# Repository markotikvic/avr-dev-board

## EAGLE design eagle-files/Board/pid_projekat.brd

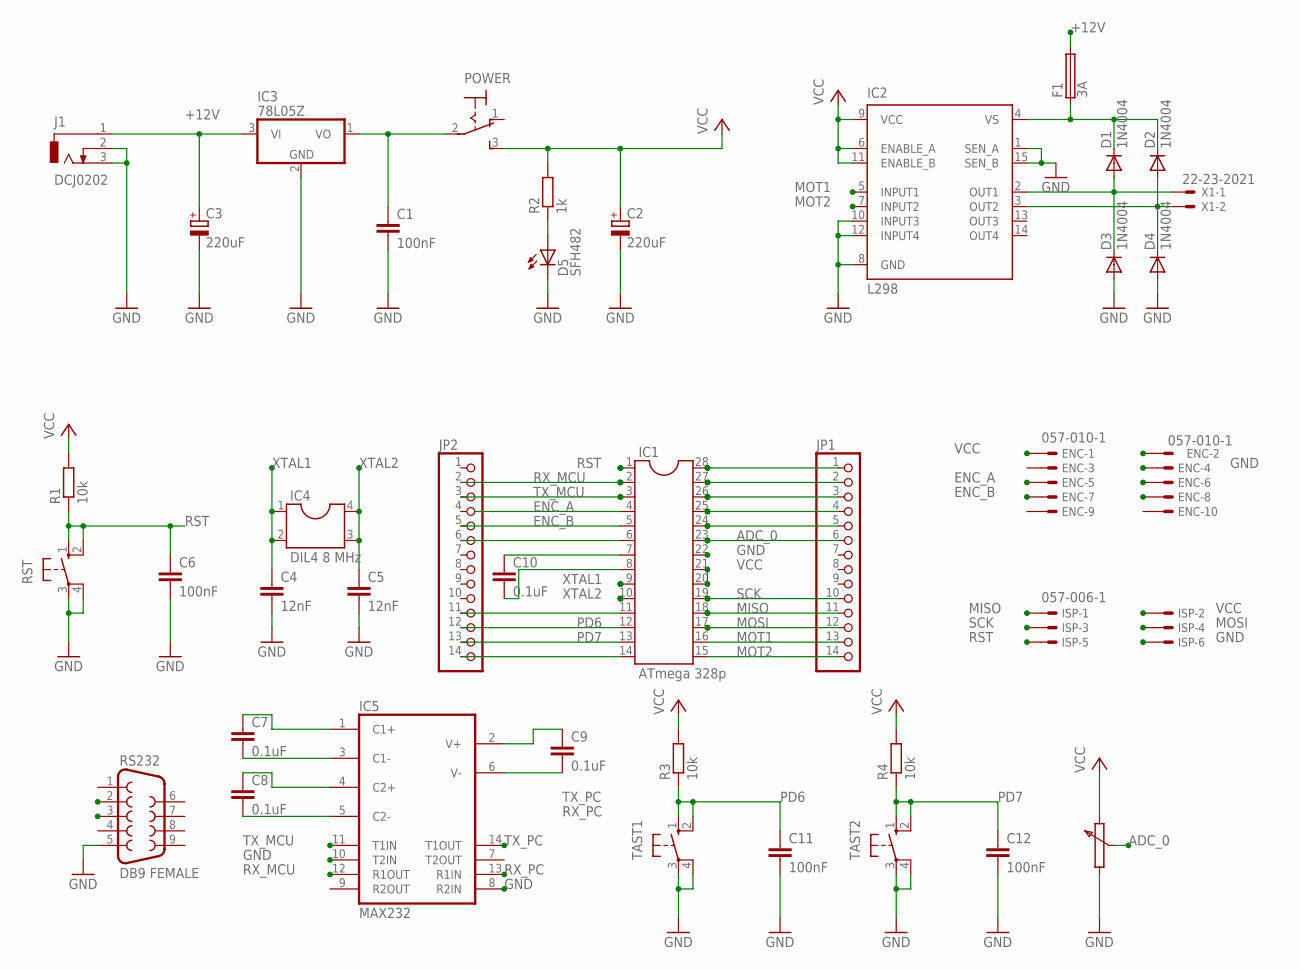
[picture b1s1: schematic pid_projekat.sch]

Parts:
C1, C6, C11, C12: 100nF; C2.5-3
C2, C3: 220uF; E2,5-6E
C4, C5: 12nF; C2.5-3
C7, C8, C9, C10: 0.1uF; C2.5-3
D1, D2, D3, D4: 1N4004; DO41-10
D5: SFH482
ENC: 057-010-1
F1: 3A; GSH15
IC1: ATmega 328p; DIL28-6
IC2: L298; MULTIWATT-15
IC3: 78L05Z; TO92
IC4: DIL4 8 MHz; DIL04
IC5: MAX232; DIL16
ISP: 057-006-1
J1: DCJ0202
JP1, JP2: PINHD-1X14; 1X14
POWER: 320-916
R1, R3, R4: 10k; 0204/7
R2: 1k; 0204/7
RS232: DB9 FEMALE; F09HP
RST: 10-XX; B3F-10XX
TAST1, TAST2: 10-XX; B3F-10XX
X1: 22-23-2021

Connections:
+12V: C3.+, F1.2, IC3.3 (VI), J1.1
ADC_0: IC1.23, JP1.6
ENC_A: ENC.5, IC1.4, IC1.26, JP1.3
ENC_AINV: ENC.6, IC1.24, JP1.5
ENC_B: ENC.7, IC1.5, IC1.25, JP1.4, JP2.5
ENC_BINV: ENC.8
GND: C1.2, C2.-, C3.-, C4.2, C5.2, C6.2, C11.2, C12.2, D3.A, D4.A, D5.K (C), ENC.4, IC1.22, IC2.1 (SEN_A), IC2.8 (GND), IC2.10 (INPUT3), IC2.12 (INPUT4), IC2.15 (SEN_B), IC3.2 (GND), IC5.8 (R2IN), IC5.10 (T2IN), IC5.15 (GND), ISP.6, J1.2, J1.3, RS232.5, RST.3, RST.4 (P1), TAST1.3, TAST1.4 (P1), TAST2.3, TAST2.4 (P1)
MISO: IC1.18, ISP.1, JP1.11
MOSI: IC1.17, ISP.4, JP1.12
MOT1: IC1.16, IC1.28, IC2.5 (INPUT1), JP1.1, JP1.13
MOT2: IC1.15, IC1.27, IC2.7 (INPUT2), JP1.2, JP1.14
MOT+: D1.A, D3.C, IC2.2 (OUT1), X1.1
MOT-: D2.A, D4.C, IC2.3 (OUT2), X1.2
unnamed: C9.2, IC5.6 (V-)
unnamed: C9.1, IC5.2 (V+)
unnamed: C1.1, IC3.1 (VO), POWER.2
unnamed: D5.A, R2.1
unnamed: IC1.6, JP2.6
unnamed: C7.2, IC5.3 (C1-)
unnamed: C7.1, IC5.1 (C1+)
unnamed: IC1.11, JP2.11
unnamed: C8.1, IC5.4 (C2+)
unnamed: C8.2, IC5.5 (C2-)
unnamed: IC1.14, JP2.14
unnamed: C10.1, IC1.7
unnamed: C10.2, IC1.8
PD6: C11.1, IC1.12, JP2.12, R3.1, TAST1.1 (S), TAST1.2 (S1)
PD7: C12.1, IC1.13, JP2.13, R4.1, TAST2.1 (S), TAST2.2 (S1)
RST: C6.1, IC1.1, ISP.5, R1.1, RST.1 (S), RST.2 (S1)
RX_MCU: IC1.2, IC5.12 (R1OUT), JP2.2
RX_PC: IC5.13 (R1IN), RS232.3
SCK: IC1.19, ISP.3, JP1.10
TX_MCU: IC1.3, IC5.11 (T1IN), JP2.3
TX_PC: IC5.14 (T1OUT), RS232.2
VCC: C2.+, ENC.1, IC1.20, IC1.21, IC2.6 (ENABLE_A), IC2.9 (VCC), IC2.11 (ENABLE_B), IC5.16 (VCC), ISP.2, POWER.3 (S), R1.2, R2.2, R3.2, R4.2
VS: D1.C, D2.C, F1.1, IC2.4 (VS)
XTAL1: C4.1, IC1.9, IC4.1, IC4.2
XTAL2: C5.1, IC1.10, IC4.3, IC4.4

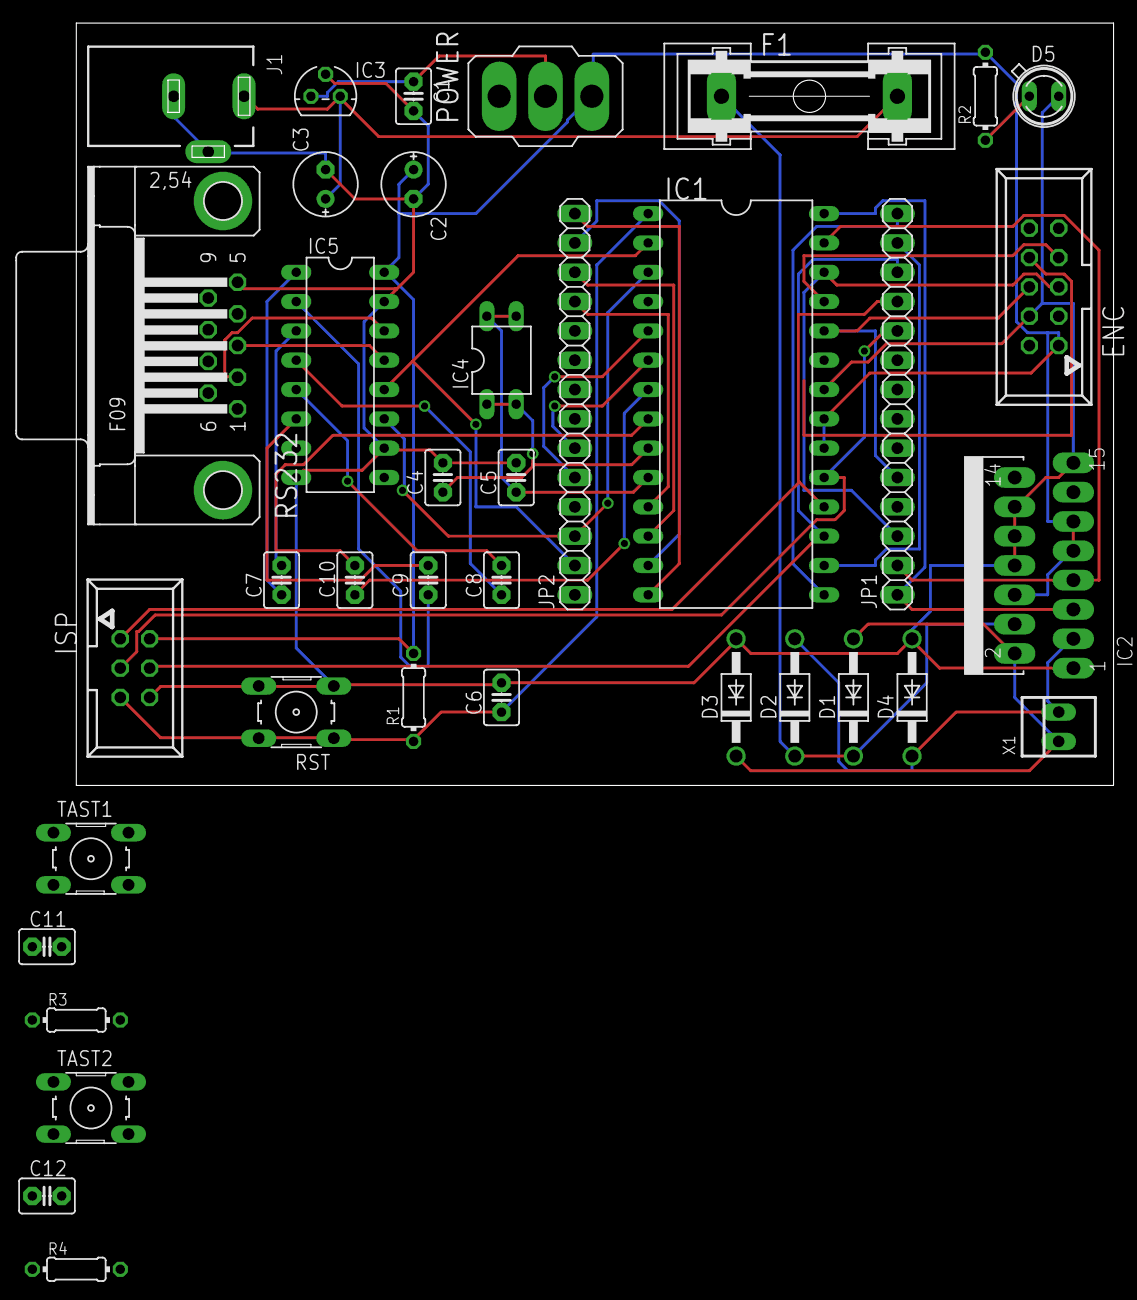
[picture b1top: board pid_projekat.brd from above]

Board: 2 copper layers, 89.8 x 66.0 mm, 38 parts (0 on the bottom side), 37 nets.

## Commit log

2015-09-02 Seconds commit
2015-09-02 Refactored all functions and variables. Unpoluted static variables. Added function poor faster pin write
2015-09-10 10.9.2015.
2015-09-10 added code directory
2015-09-10 убачен пример за серијску комуникацију
    измењена уарт библиотека
2015-09-10 gpio_doc; separted motor functions
2015-09-10 example finished
2015-09-10 gpio_example
2015-09-10 finished motor example
2015-09-10 GPIO
2015-09-10 MOTOR
2015-09-10 ignoring .atsuo files
2015-09-10 pwm example, missing doc
2015-09-12 pwm example done
2015-09-12 probano na motorima
2015-09-12 pwm tested with motor
2015-09-12 ext counter example started
2015-09-13 ext counter completed
2015-09-13 positional pid done
2015-09-13 backup before develop merge
2015-09-13 All done but ADC example
2015-09-13 Updated all libs
2015-09-13 pid documentation
2015-09-13 updated pid lib in avr_dev_board
2015-09-13 paralel blinking example
2015-09-13 adc example done
2015-09-15 final touches
2015-09-21 21-09-2015 backup
2015-09-22 added ext counter 2 example
2015-09-22 final
2016-06-18 cleaned up... a lot
2016-06-18 restructured project tree
